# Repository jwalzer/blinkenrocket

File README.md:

# blinkenrocket
Yet another kit to teach soldering to people

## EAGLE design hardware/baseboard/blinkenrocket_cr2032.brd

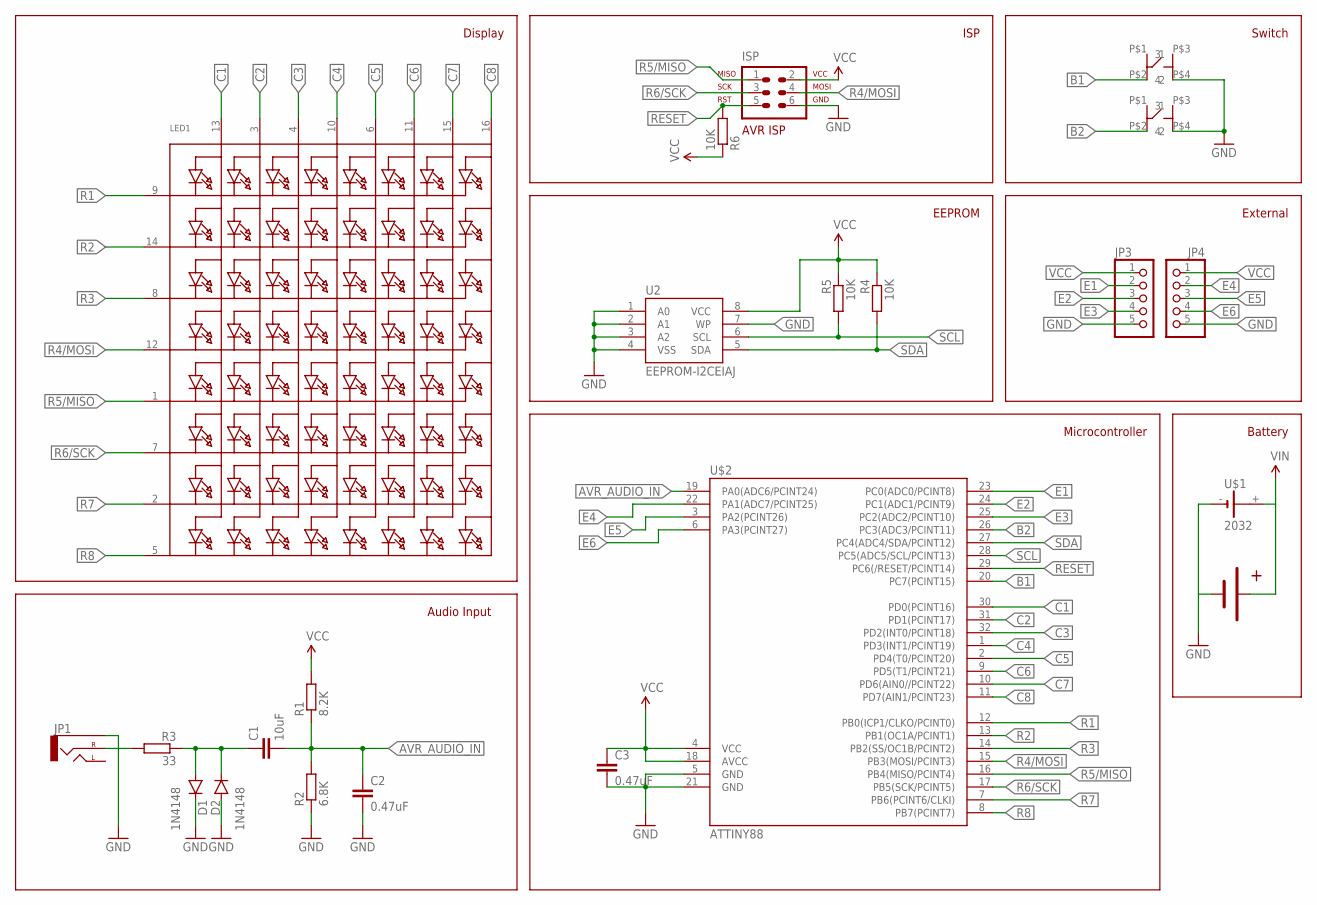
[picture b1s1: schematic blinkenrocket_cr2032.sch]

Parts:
C1: 10uF; C0805K
C2, C3: 0.47uF; C0805K
D1, D2: 1N4148; SOD-323
ISP: AVR-ISP-6VERT; AVR-ISP-6
JP1: AUDIO-JACKPTH; AUDIO-JACK
JP3, JP4: PINHD-1X05_2.54-S; 1X05-S
LED1: SEGMENT_8X8_ROWCATHODEM12A881UR; SEGMENT_BL-M12A881UR
R1: 8.2K; M0805
R2: 6.8K; M0805
R3: 33; M0805
R4, R5, R6: 10K; M0805
SW1, SW2: SWITCH-4POMRON-6-6-SWITCH; 4P-OMRON-6-6-SWITCH
U2: EEPROM-I2CEIAJ; SO08-EIAJ
U$1: 2032; KZH20SMD
U$2: ATTINY88; TQFP32-08
U$3: BATTERYPAD

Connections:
AVR_AUDIO_IN: C1.2, C2.1, R1.1, R2.2, U$2.19 (PA0(ADC6/PCINT24))
B1: SW2.P$2 (2), U$2.20 (PC7(PCINT15))
B2: SW1.P$2 (2), U$2.26 (PC3(ADC3/PCINT11))
C1: LED1.13 (A1), U$2.30 (PD0(PCINT16))
C2: LED1.3 (A2), U$2.31 (PD1(PCINT17))
C3: LED1.4 (A3), U$2.32 (PD2(INT0/PCINT18))
C4: LED1.10 (A4), U$2.1 (PD3(INT1/PCINT19))
C5: LED1.6 (A5), U$2.2 (PD4(T0/PCINT20))
C6: LED1.11 (A6), U$2.9 (PD5(T1/PCINT21))
C7: LED1.15 (A7), U$2.10 (PD6(AIN0//PCINT22))
C8: LED1.16 (A8), U$2.11 (PD7(AIN1/PCINT23))
E1: JP3.2, U$2.23 (PC0(ADC0/PCINT8))
E2: JP3.3, U$2.24 (PC1(ADC1/PCINT9))
E3: JP3.4, U$2.25 (PC2(ADC2/PCINT10))
E4: JP4.2, U$2.22 (PA1(ADC7/PCINT25))
E5: JP4.3, U$2.3 (PA2(PCINT26))
E6: JP4.4, U$2.6 (PA3(PCINT27))
GND: C2.2, C3.2, D1.C, D2.A, ISP.6, JP1.SLEEVE, JP3.5, JP4.5, R2.1, SW1.P$4 (4), SW2.P$4 (4), U2.1 (A0), U2.2 (A1), U2.3 (A2), U2.4 (VSS), U2.7 (WP), U$1.-, U$2.5 (GND), U$2.21 (GND), U$3.-VE
unnamed: JP1.RING (RIGHT), R3.2
unnamed: C1.1, D1.A, D2.C, R3.1
R1: LED1.9 (K1), U$2.12 (PB0(ICP1/CLKO/PCINT0))
R2: LED1.14 (K2), U$2.13 (PB1(OC1A/PCINT1))
R3: LED1.8 (K3), U$2.14 (PB2(SS/OC1B/PCINT2))
R4/MOSI: ISP.4, LED1.12 (K4), U$2.15 (PB3(MOSI/PCINT3))
R5/MISO: ISP.1, LED1.1 (K5), U$2.16 (PB4(MISO/PCINT4))
R6/SCK: ISP.3, LED1.7 (K6), U$2.17 (PB5(SCK/PCINT5))
R7: LED1.2 (K7), U$2.7 (PB6(PCINT6/CLKI))
R8: LED1.5 (K8), U$2.8 (PB7(PCINT7))
RESET: ISP.5, R6.2, U$2.29 (PC6(/RESET/PCINT14))
SCL: R5.2, U2.6 (SCL), U$2.28 (PC5(ADC5/SCL/PCINT13))
SDA: R4.2, U2.5 (SDA), U$2.27 (PC4(ADC4/SDA/PCINT12))
VCC: C3.1, ISP.2, JP3.1, JP4.1, R1.2, R4.1, R5.1, R6.1, U2.8 (VCC), U$1.+, U$2.4 (VCC), U$2.18 (AVCC), U$3.+VE

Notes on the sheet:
Audio Input
Display
ISP
Switch
Battery
EEPROM
Microcontroller
External

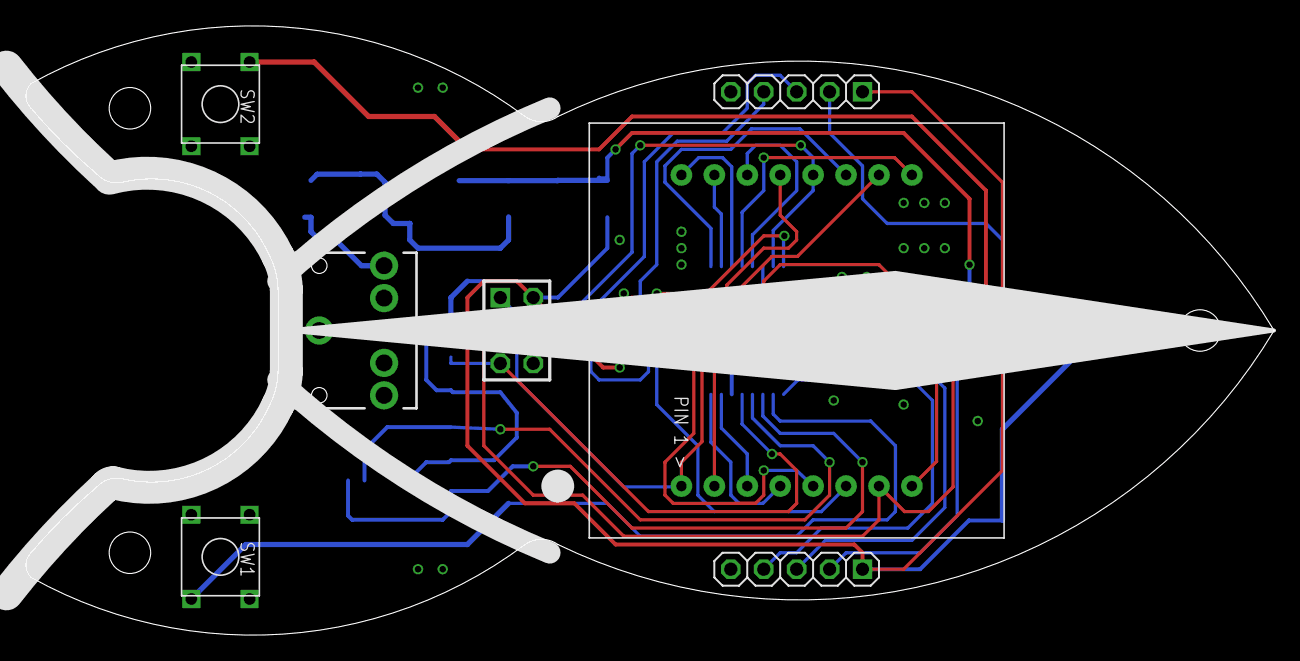
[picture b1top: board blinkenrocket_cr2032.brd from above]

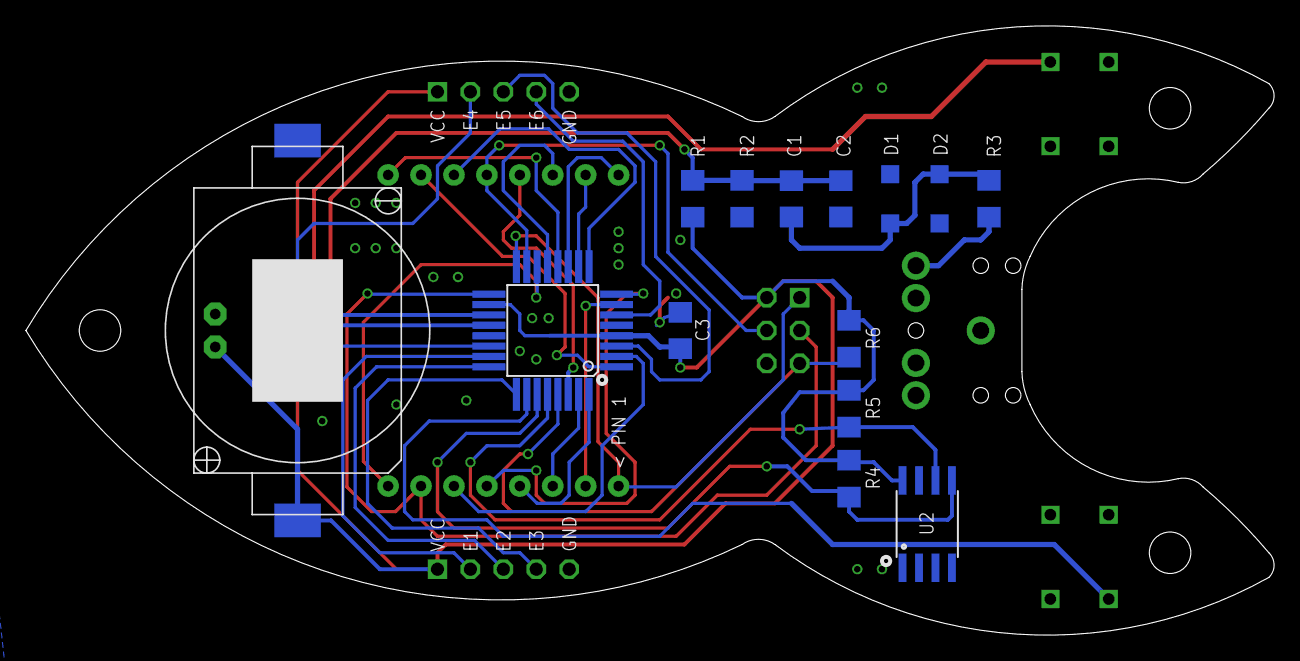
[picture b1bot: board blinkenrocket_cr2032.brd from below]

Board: 2 copper layers, 96.3 x 47.0 mm, 22 parts (15 on the bottom side), 32 nets.

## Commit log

2015-11-28 add schematic
2015-11-28 added soldering comic in GERMAN
2015-11-28 renamed to clarify language
2015-11-28 add tagsu-avr-modem submodule
2015-12-31 1206 instead of 0805 - this is easier to solder actually...
2015-12-31 more symmetric
2015-12-31 add pdf of schematic for convenience
2016-01-03 Web dotmatrix test
2016-01-03 move some parts around
2016-01-07 first prototype web-IDE layout
2016-01-08 add buttons (delete, add), add animation controls and modals
2016-01-09 some refactor action
2016-03-01 extracted partlist for soldering from the eagle-file

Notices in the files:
parts and their libraries:
SparkFun-DigitalIC: Licensing: Creative Commons ShareAlike 4.0 International - https://creativecommons.org/licenses/by-sa/4.0
computronics.com.au: ©Computronics Corporation Ltd, 2004
